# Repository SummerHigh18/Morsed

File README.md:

# Morsed

***A Morse Code learning PCB!***

This is a PCB having an OLED screen with mainly 3 features we can say:
- Live Decode: Here we press buttons, and it decodes it into letters only. (dash[-] and dot[.])

- Word Decode: This is similar to the one above, and makes much more sense for using. The differernce is just that this makes up a whole word, and not just live decoding into letters.

- A readable cheat-sheet where we can access every letter and it's corresponding Morse code.

- Lastly we have a secret screen where if someone inputs 'GAME' in the Word Decode, it pushes to a simple game!

This is what the PCB looks like!  

The bottom 2 buttons are for dot and dash.  
While the butoons on the right are for Enter and Space!  
The one on the right I might change as per convinience to other functions too in future.

### AI Usage
I used AI for microcontroller purposes and schematic verification.
This usage can be confirmed in the Lapse Recordings.

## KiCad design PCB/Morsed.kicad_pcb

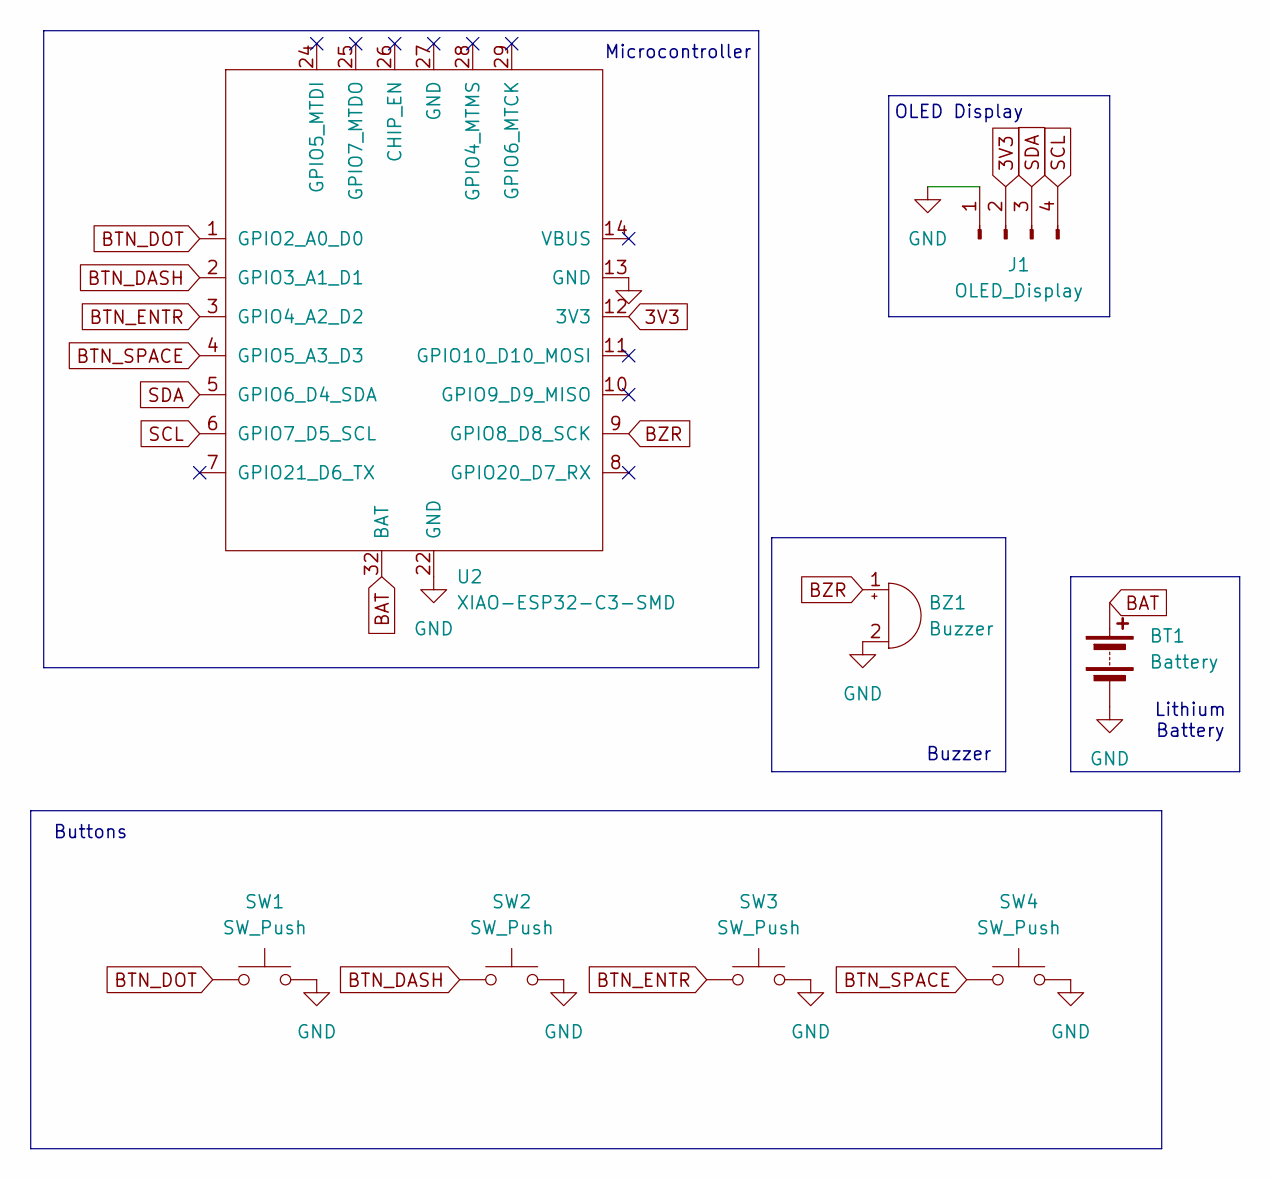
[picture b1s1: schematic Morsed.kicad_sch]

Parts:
BT1: Battery; JST_EH_B2B-EH-A_1x02_P2.50mm_Vertical
BZ1: Buzzer; Buzzer_12x9.5RM7.6
J1: OLED_Display; MODULE_DM-OLED096-636
SW1, SW2, SW3, SW4: SW_Push; SW_PUSH_6mm
U2: XIAO-ESP32-C3-SMD; XIAO-ESP32-C3-DIP-SMD

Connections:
3V3: J1.2, U2.12 (3V3)
BAT: BT1.1 (+), U2.32 (BAT)
BTN_DASH: SW2.1, U2.2 (GPIO3_A1_D1)
BTN_DOT: SW1.1, U2.1 (GPIO2_A0_D0)
BTN_ENTR: SW3.1, U2.3 (GPIO4_A2_D2)
BTN_SPACE: SW4.1, U2.4 (GPIO5_A3_D3)
BZR: BZ1.1 (+), U2.9 (GPIO8_D8_SCK)
GND: BT1.2 (-), BZ1.2 (-), J1.1, SW1.2, SW2.2, SW3.2, SW4.2, U2.13 (GND), U2.22 (GND)
SCL: J1.4, U2.6 (GPIO7_D5_SCL)
SDA: J1.3, U2.5 (GPIO6_D4_SDA)

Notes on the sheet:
Buttons
Lithium Battery
OLED Display
Buzzer
Microcontroller

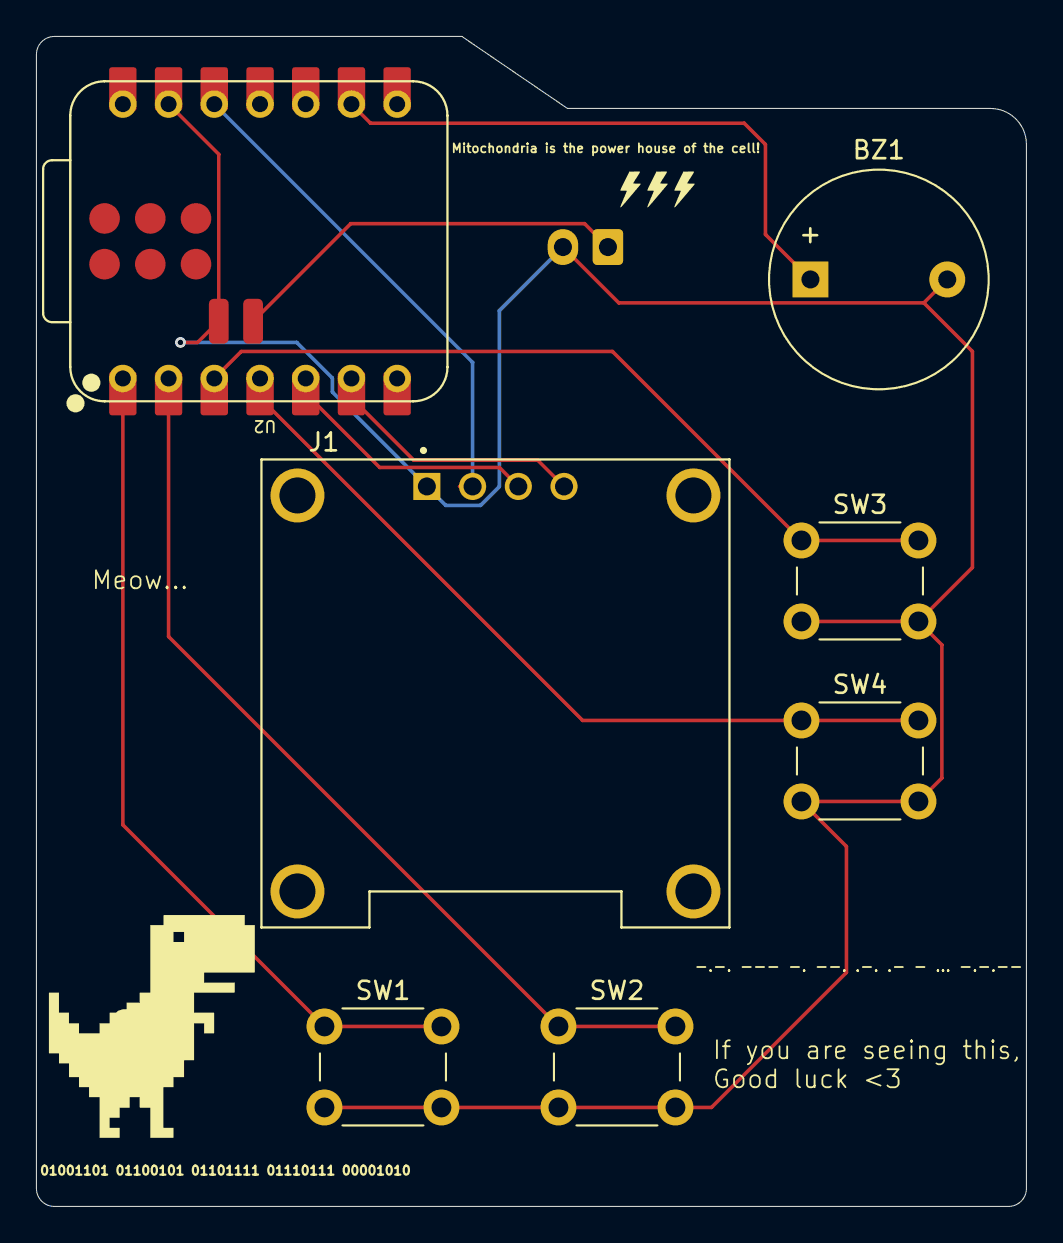
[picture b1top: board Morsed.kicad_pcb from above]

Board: 2 copper layers, 55.0 x 65.0 mm, 8 parts (1 on the bottom side), 10 nets.

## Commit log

2026-05-01 Add README.md
2026-05-04 Added Jornal.md with images and uploaded KiCAD files
2026-05-04 Images were not appearing; So Fixed the image path
2026-05-04 Rename journal.md to JOURNAL.md
2026-05-04 Add AI usage section to README
    Added section on AI usage for microcontroller and schematic verification.
